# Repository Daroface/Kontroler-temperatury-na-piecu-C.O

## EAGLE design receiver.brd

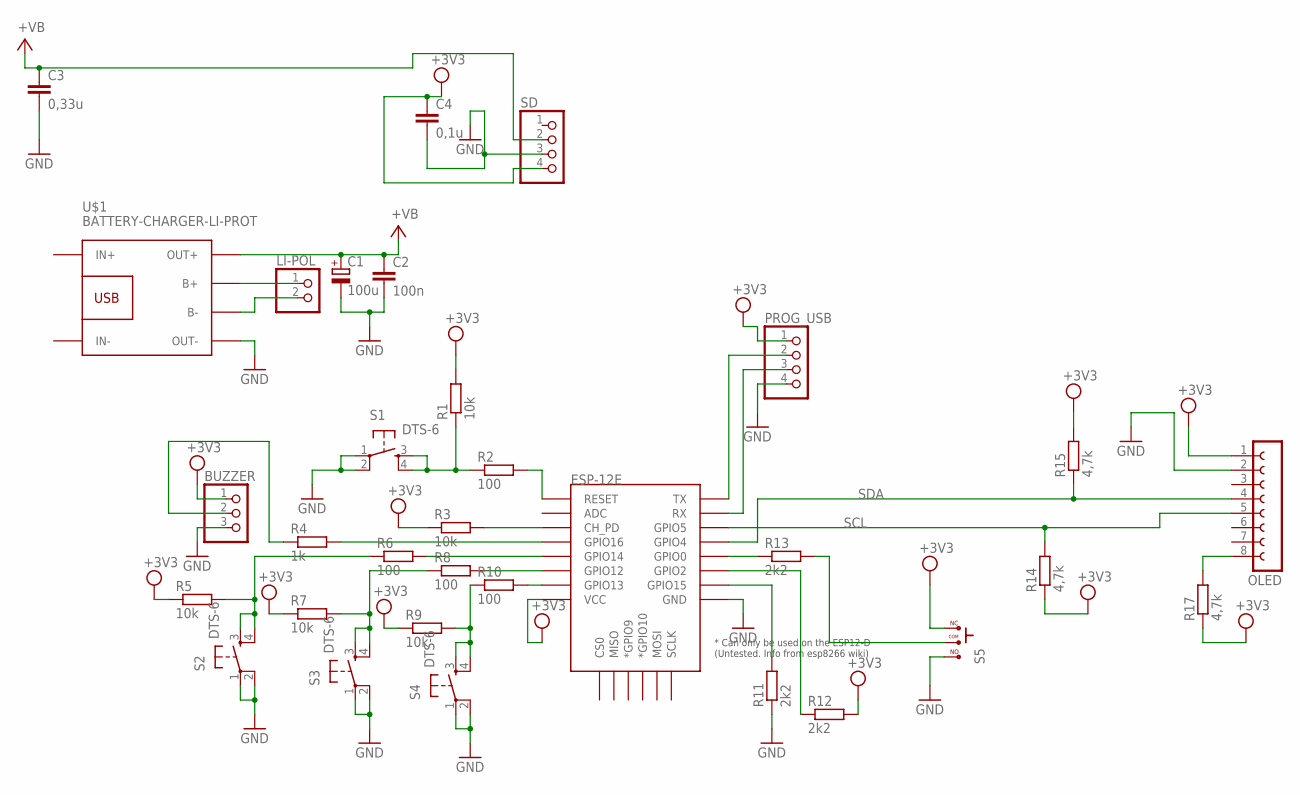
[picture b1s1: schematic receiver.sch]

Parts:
BUZZER: PINHD-1X3/90; 1X03/90
C1: 100u; E2,5-6
C2: 100n; C025-025X050
C3: 0,33u; C025-025X050
C4: 0,1u; C025-025X050
ESP-12E: ESP12ESMD; ESP12E-SMD
LI-POL: PINHD-1X2; 1X02
OLED: FE08-1; FE08
PROG_USB: PINHD-1X4; 1X04
R1, R3, R5, R7, R9: 10k; 0204/7
R2, R6, R8, R10: 100; 0204/7
R4: 1k; 0204/7
R11, R12, R13: 2k2; 0204/7
R14, R15, R17: 4,7k; 0204/7
S1, S2, S3, S4: DTS-6
S5: -SWITCH; CON3
SD: PINHD-1X4; 1X04
U$1: BATTERY-CHARGER-LI-PROT

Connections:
GND: BUZZER.3, C1.-, C2.2, C3.2, C4.2, ESP-12E.GND, OLED.2, PROG_USB.4, R11.1, S1.1, S1.2, S2.1, S2.2, S3.1, S3.2, S4.1, S4.2, S5.P$3 (3), SD.3, U$1.OUT-
unnamed: ESP-12E.CH_PD, R3.2
unnamed: R13.2, S5.P$2 (2)
unnamed: ESP-12E.GPIO2, R12.1
unnamed: ESP-12E.TXD0 (TX), PROG_USB.2
unnamed: ESP-12E.RXD0 (RX), PROG_USB.3
unnamed: ESP-12E.GPIO12, R8.2
unnamed: OLED.8, R17.2
unnamed: LI-POL.1, U$1.B+
unnamed: ESP-12E.GPIO13, R10.2
unnamed: ESP-12E.GPIO15, R11.2
unnamed: ESP-12E.GPIO14, R6.2
unnamed: R7.2, R8.1, S3.3, S3.4
unnamed: R1.1, R2.1, S1.3, S1.4
unnamed: ESP-12E.GPIO16, R4.2
unnamed: LI-POL.2, U$1.B-
unnamed: ESP-12E.RESET, R2.2
unnamed: BUZZER.2, R4.1
unnamed: ESP-12E.GPIO0, R13.1
unnamed: R9.2, R10.1, S4.3, S4.4
unnamed: R5.2, R6.1, S2.3, S2.4
SCL: ESP-12E.GPIO5, OLED.5, R14.2
SDA: ESP-12E.GPIO4, OLED.4, R15.1
V+: C1.+, C2.1, C3.1, SD.2, U$1.OUT+
VCC: BUZZER.1, C4.1, ESP-12E.VCC, OLED.1, PROG_USB.1, R1.2, R3.1, R5.1, R7.1, R9.1, R12.2, R14.1, R15.2, R17.1, S5.P$1 (1), SD.4

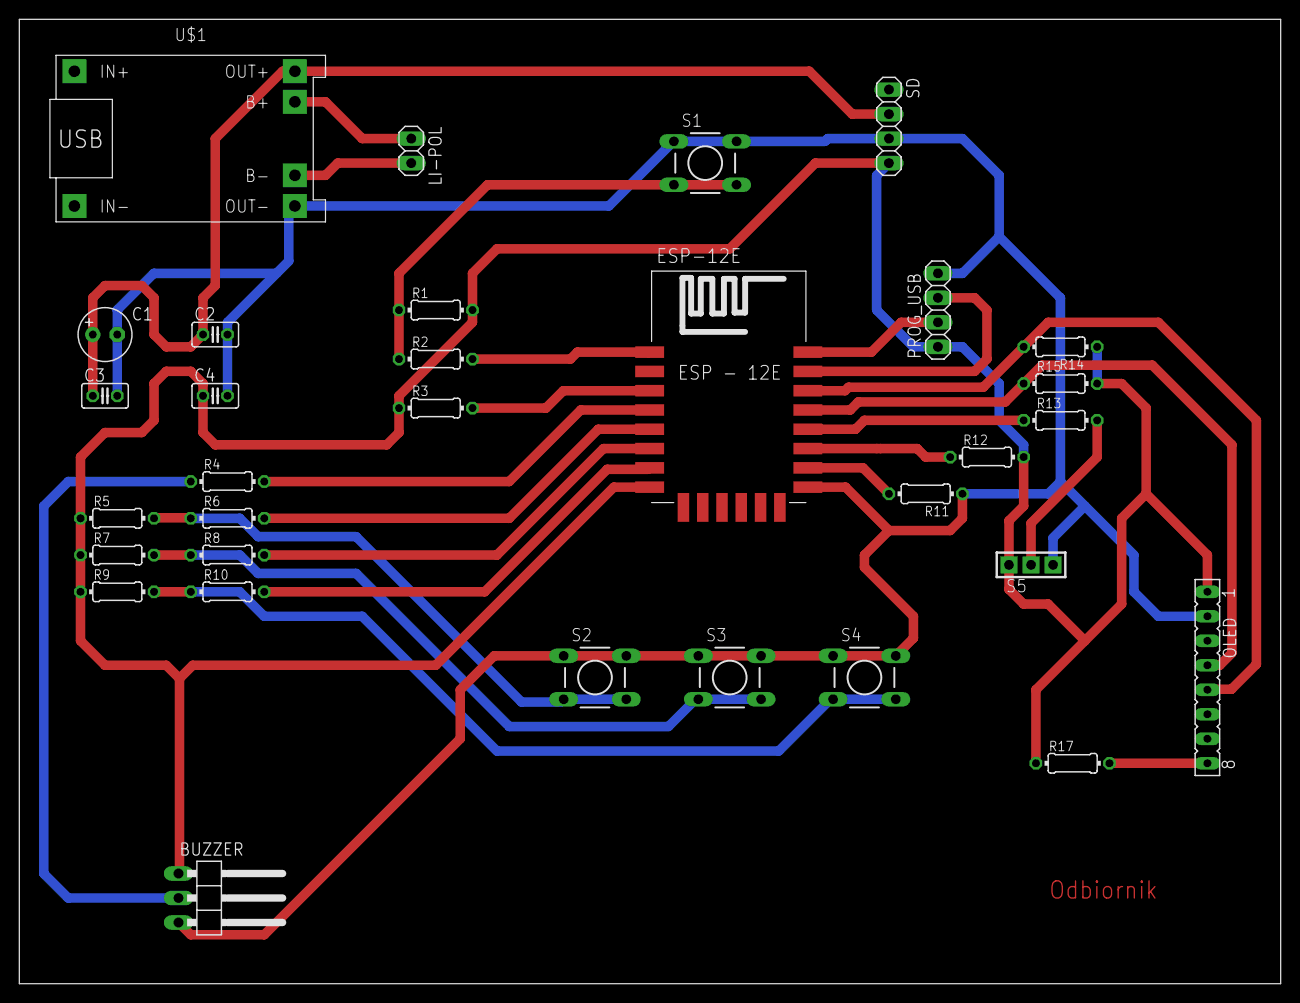
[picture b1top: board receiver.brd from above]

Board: 2 copper layers, 130.8 x 100.0 mm, 32 parts (0 on the bottom side), 25 nets.

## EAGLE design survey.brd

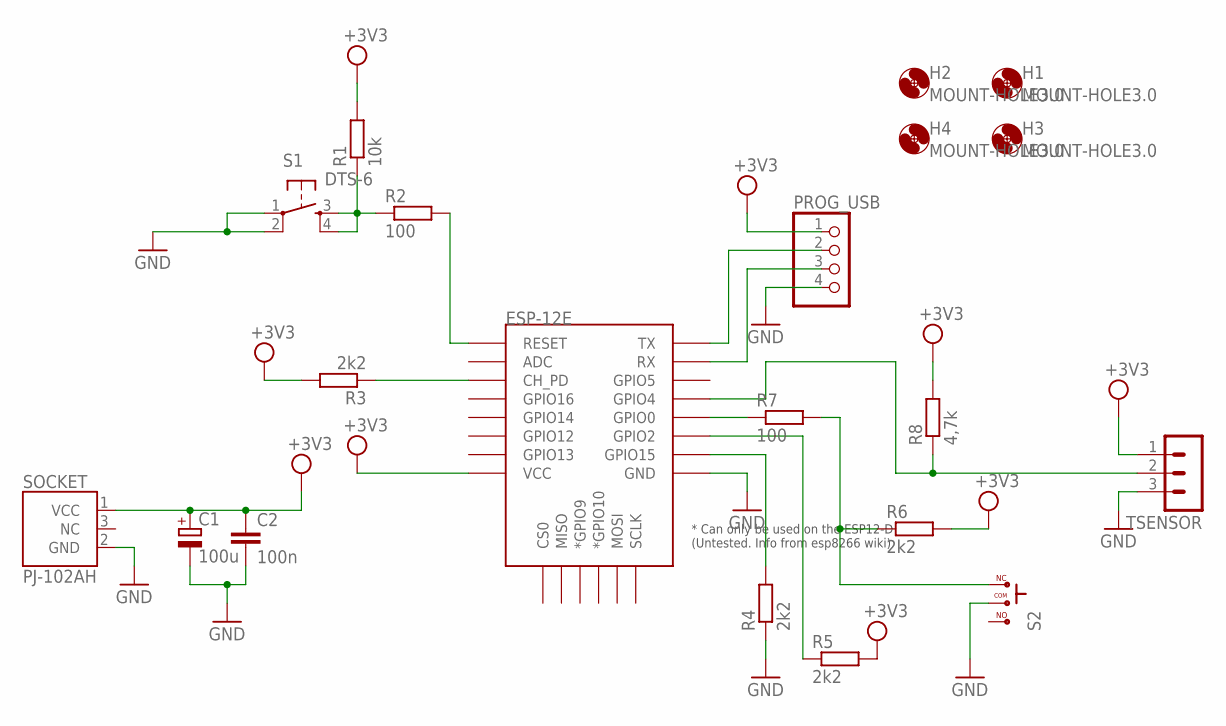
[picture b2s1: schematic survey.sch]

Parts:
C1: 100u; E2,5-6
C2: 100n; C025-025X050
ESP-12E: ESP12ESMD; ESP12E-SMD
H1, H2, H3, H4: MOUNT-HOLE3.0; 3,0
PROG_USB: PINHD-1X4; 1X04
R1: 10k; 0204/7
R2, R7: 100; 0204/7
R3, R4, R5, R6: 2k2; 0204/7
R8: 4,7k; 0204/7
S1: DTS-6
S2: -SWITCH; CON3
SOCKET: PJ-102AH
TSENSOR: MA03-1

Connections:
GND: C1.-, C2.2, PROG_USB.4, R4.1, S1.1, S1.2, S2.P$2 (2), SOCKET.2 (GND), TSENSOR.3
unnamed: ESP-12E.GPIO2, R5.1
unnamed: ESP-12E.CH_PD, R3.1
unnamed: ESP-12E.TXD0 (TX), PROG_USB.2
unnamed: ESP-12E.RXD0 (RX), PROG_USB.3
unnamed: ESP-12E.GPIO4, R8.1, TSENSOR.2
unnamed: R6.1, R7.2, S2.P$1 (1)
unnamed: ESP-12E.GPIO15, R4.2
unnamed: ESP-12E.RESET, R2.2
unnamed: R1.1, R2.1, S1.3, S1.4
unnamed: ESP-12E.GPIO0, R7.1
VCC: C1.+, C2.1, ESP-12E.VCC, PROG_USB.1, R1.2, R3.2, R5.2, R6.2, R8.2, SOCKET.1 (VCC), TSENSOR.1

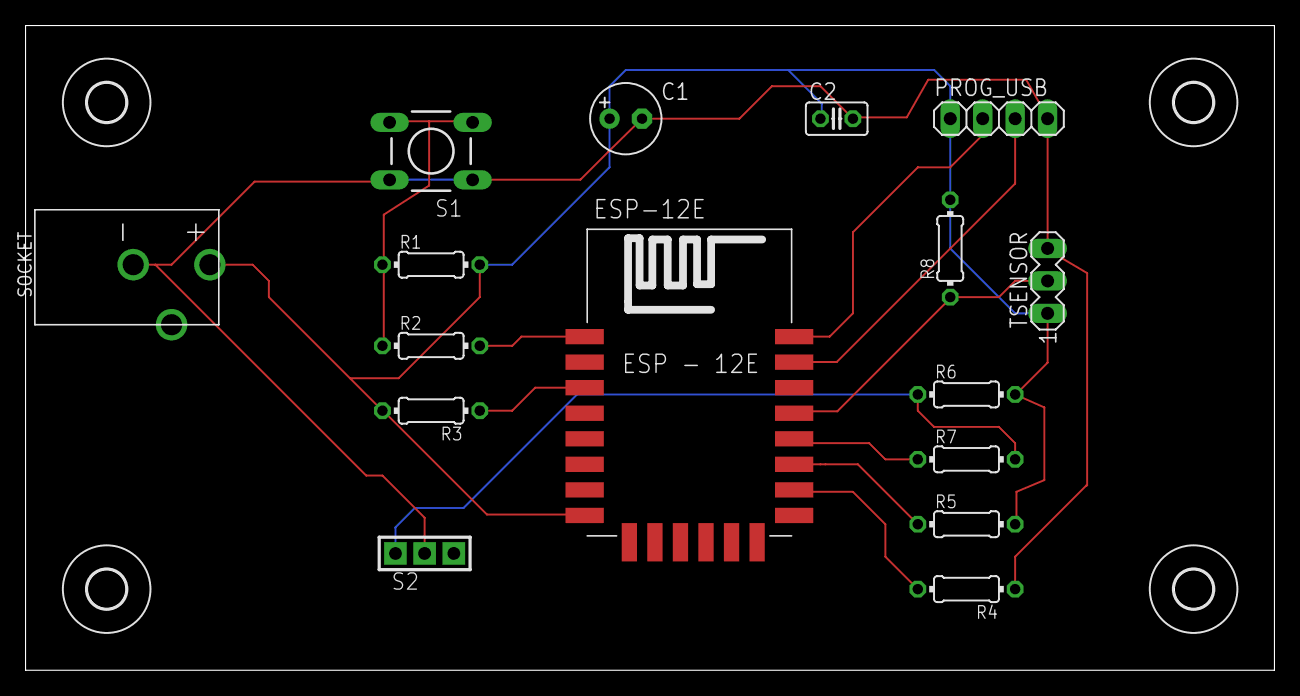
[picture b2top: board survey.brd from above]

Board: 2 copper layers, 97.8 x 50.5 mm, 20 parts (0 on the bottom side), 12 nets.

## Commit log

2018-03-19 inital commint
2018-03-19 add receiver's shematic
2018-03-19 Added receiver's schematic.
2018-03-20 Improved some bugs in receiver's and survey's schematic.
2018-04-08 Corrected reset pin connection and added pull-up resistor to temperature sensor.
2018-04-08 Corrected VCC pin connection, added level shifter to communicate micro controller with LCD, changed voltage supply marks, corrected connections of buttons to micro controller, added library with leve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
2018-04-10 Added to receiver pull-up resitors, added documentation of LCD, corrected reset pin connection.
2018-04-10 Corrected Reset pin connection, changed stablizer on step yp/step down converter.
2018-04-30 Changed 5V LCD on 3,3V LCd, replaced 5V from schematic on 3,3V.
2018-04-30 Added third button to control device, changed labels of capacitors.
2018-04-30 Added charger.
2018-04-30 Renamed labels.
2018-04-30 added buzzer.
2018-04-30 Added resisotr to busser input line.
2018-05-24 Changed some resistors from 10k for 2k2 and added resisors 100 to reset and gpio0 pin.
2018-05-24 Changed 2pins tact switches for 4pins tact switches.
2018-05-24 Changed OLED socket from 4 pins on 8 pins.
2018-05-24 Changed labels.
2018-05-24 Created the survey's board.
2018-05-24 Added .gitignore.
2018-05-28 Changed +3V7 for V_BAT and deleted some errors.
2018-06-01 Boards and schematics are done.
2018-06-01 Last corrects.
2018-07-20 Corrected programming switch connection.
2018-07-20 Removed pdfs and renamed survey to transmiter.
2018-07-20 Added software to receiver and transmiter.
2018-08-21 Changed names of the folders which includ soft.
2018-08-21 Added comments.
2018-08-21 Added library for control OLED.
2018-09-01 Added communication between client and server. Temperature is read and send correctly.
2018-09-01 Library to control ds18b20.
2018-09-08 Prepared to connect OLED.
2018-09-10 Modified way of printing data on OLED.

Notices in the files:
parts and their libraries:
diy-modules: Released under the Creative Commons Attribution 4.0 International License: http://creativecommons.org/licenses/by/4.0
